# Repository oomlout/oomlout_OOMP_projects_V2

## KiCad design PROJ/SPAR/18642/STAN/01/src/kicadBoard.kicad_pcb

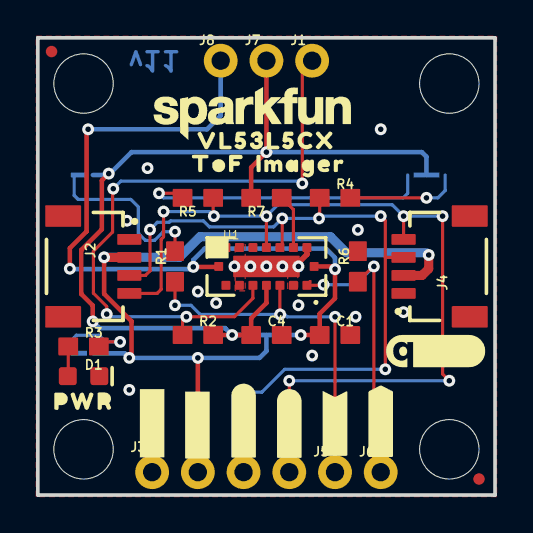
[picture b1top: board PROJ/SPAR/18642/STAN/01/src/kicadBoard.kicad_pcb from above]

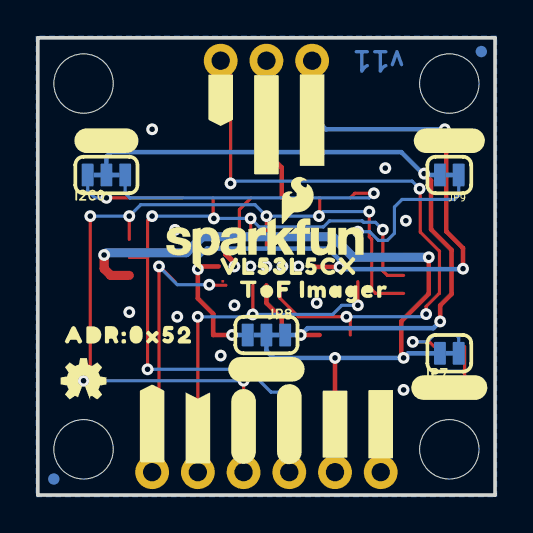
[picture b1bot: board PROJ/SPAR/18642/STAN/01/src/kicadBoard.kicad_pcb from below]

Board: 2 copper layers, 25.4 x 25.4 mm, 63 parts (25 on the bottom side), 15 nets.

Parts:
C1: 4.7uF; 0603
C4: 0.1uF; 0603
D1: RED; LED-0603
FRAME1: FRAME-LETTER; CREATIVE_COMMONS
I2C0: JUMPER-SMT_3_2-NC_TRACE_SILK; SMT-JUMPER_3_2-NC_TRACE_SILK
J1, J5, J6, J7, J8: 1X01_NO_SILK
J2, J4: JST04_1MM_RA
J3: PTH; 1X04_NO_SILK
JP1, JP2, JP5, JP6: FIDUCIALUFIDUCIAL; MICRO-FIDUCIAL
JP3, JP4, JP10, JP11: STAND-OFF
JP7: PWR_LED; SMT-JUMPER_2_NC_TRACE_SILK
JP8: PSU; SMT-JUMPER_3_2-NC_TRACE_SILK
JP9: INT; SMT-JUMPER_2_NC_TRACE_SILK
LOGO1: OSHW-LOGOMINI; OSHW-LOGO-MINI
LOGO3: QWIIC_LOGO_CONNECTOR; QWIIC_5.5MM
R1, R2, R6, R7: 47k; 0603
R3: 1k; 0603
R4, R5: 2.2k; 0603
U1: VL53L5CX
U$1: SFE_LOGO_NAME.1_INCH; SFE_LOGO_NAME_.1
U$2: SFE_LOGO_NAME_FLAME.1_INCH; SFE_LOGO_NAME_FLAME_.1
U$3, U$21: #3V3#13
U$4: PWR12
U$5: #LED#10
U$6: #INT#0
U$7: #RST#1
U$8: #INT_#0
U$9: #RST_#1
U$10: ##LP##2
U$11: #INT#1
U$12: #VDDA#0
U$13: ADR#0X520
U$14: #VDDIO#1
U$15: #PSU#0
U$16: #I�C#0
U$17, U$19: VL53L5CX0
U$18, U$22: IMAGER2
U$20, U$23: TOF1
U$24: #SCL#1
U$25: #SDA#0
U$26, U$30: #GND#62130
U$28: #SDA#62131
U$29: #SCL#62132

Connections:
3.3V: J2.2, J3.2, J4.2, JP7.2, JP8.2
GND: C1.2, C4.2, D1.C, J2.1, J3.1, J4.1, R6.2, U1.A2, U1.A6, U1.A7, U1.B4, U1.C1, U1.C6, U1.C7
INT: J5.1, R1.1, U1.A3
unnamed: I2C0.1, R5.2
unnamed: I2C0.3, R4.2
unnamed: D1.A, R3.1
unnamed: JP9.1, R1.2
unnamed: JP7.1, R3.2
unnamed: R7.1, U1.C2
RST: J6.1, R6.1, U1.A1
SCL: J2.4, J3.4, J4.4, R5.1, U1.C4
SDA: J2.3, J3.3, J4.3, R4.1, U1.C3
VDDA: C1.1, J8.1, JP8.1, U1.B1, U1.B7
VDDIO: C4.1, I2C0.2, J7.1, JP8.3, JP9.2, R2.2, R7.2, U1.A4
~LP: J1.1, R2.1, U1.A5

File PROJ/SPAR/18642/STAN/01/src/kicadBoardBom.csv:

"Id";"Designator";"Package";"Quantity";"Designation";"Supplier and ref";
1;"R2,R6,R1,R7";"0603";4;"47k";;;
2;"U$7";"#RST#1";1;"";;;
3;"U$21,U$3";"#3V3#13";2;"";;;
4;"J1,J5,J8,J6,J7";"1X01_NO_SILK";5;"";;;
5;"C4";"0603";1;"0.1uF";;;
6;"JP10,JP3,JP11,JP4";"STAND-OFF";4;"STAND-OFF";;;
7;"FRAME1";"CREATIVE_COMMONS";1;"FRAME-LETTER";;;
8;"LOGO3";"QWIIC_5.5MM";1;"QWIIC_LOGO_CONNECTOR";;;
9;"J4,J2";"JST04_1MM_RA";2;"";;;
10;"J3";"1X04_NO_SILK";1;"PTH";;;
11;"D1";"LED-0603";1;"RED";;;
12;"R3";"0603";1;"1k";;;
13;"U$17,U$19";"VL53L5CX0";2;"";;;
14;"U$26,U$30";"#GND#62130";2;"";;;
15;"U$23,U$20";"TOF1";2;"";;;
16;"JP2,JP6,JP5,JP1";"MICRO-FIDUCIAL";4;"FIDUCIALUFIDUCIAL";;;
17;"U$4";"PWR12";1;"";;;
18;"U$28";"#SDA#62131";1;"";;;
19;"U$6";"#INT#0";1;"";;;
20;"R5,R4";"0603";2;"2.2k";;;
21;"U$29";"#SCL#62132";1;"";;;
22;"U1";"VL53L5CX";1;"VL53L5CX";;;
23;"U$1";"SFE_LOGO_NAME_.1";1;"SFE_LOGO_NAME.1_INCH";;;
24;"C1";"0603";1;"4.7uF";;;
25;"U$18,U$22";"IMAGER2";2;"";;;
26;"U$2";"SFE_LOGO_NAME_FLAME_.1";1;"SFE_LOGO_NAME_FLAME.1_INCH";;;
27;"LOGO1";"OSHW-LOGO-MINI";1;"OSHW-LOGOMINI";;;
28;"U$12";"#VDDA#0";1;"";;;
29;"U$15";"#PSU#0";1;"";;;
30;"U$8";"#INT_#0";1;"";;;
31;"U$5";"#LED#10";1;"";;;
32;"JP7";"SMT-JUMPER_2_NC_TRACE_SILK";1;"PWR_LED";;;
33;"U$10";"##LP##2";1;"";;;
34;"U$24";"#SCL#1";1;"";;;
35;"JP9";"SMT-JUMPER_2_NC_TRACE_SILK";1;"INT";;;
36;"U$11";"#INT#1";1;"";;;
37;"U$14";"#VDDIO#1";1;"";;;
38;"JP8";"SMT-JUMPER_3_2-NC_TRACE_SILK";1;"PSU";;;
39;"U$25";"#SDA#0";1;"";;;
40;"I2C0";"SMT-JUMPER_3_2-NC_TRACE_SILK";1;"JUMPER-SMT_3_2-NC_TRACE_SILK";;;
41;"U$9";"#RST_#1";1;"";;;
42;"U$13";"ADR#0X520";1;"";;;
43;"U$16";"#I�C#0";1;"";;;

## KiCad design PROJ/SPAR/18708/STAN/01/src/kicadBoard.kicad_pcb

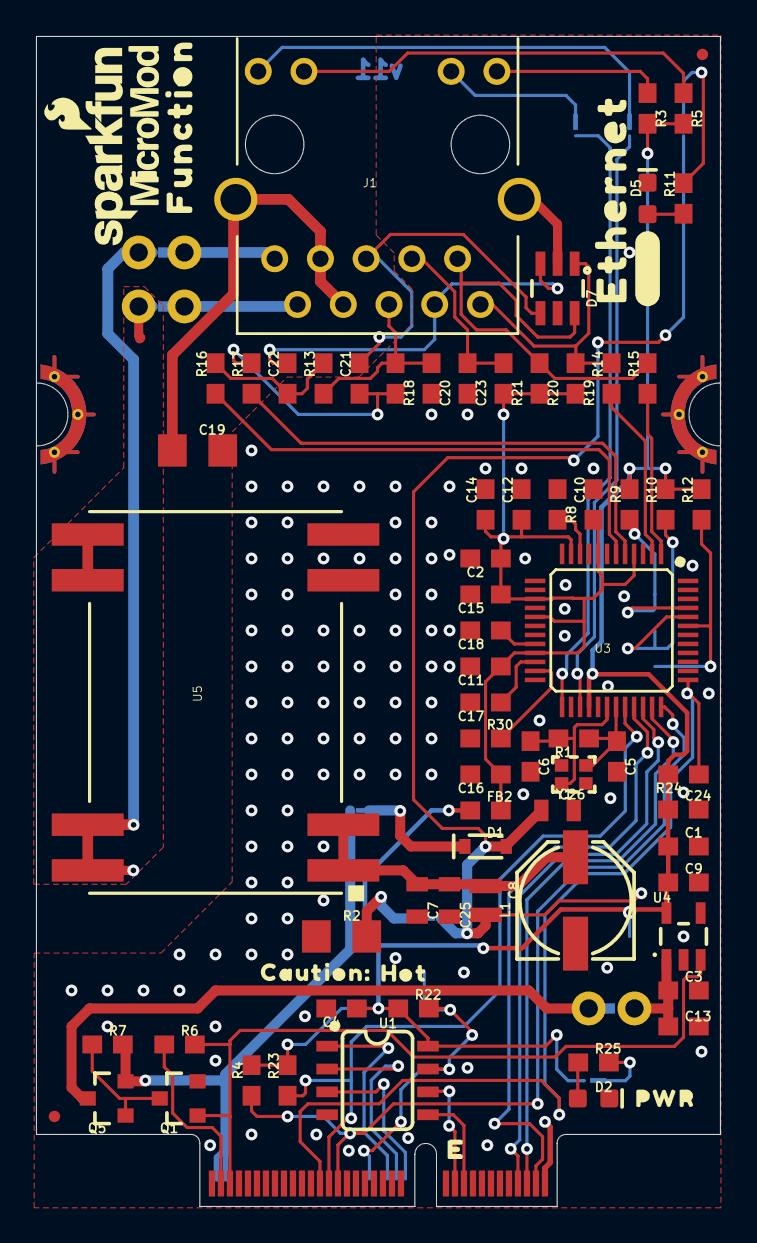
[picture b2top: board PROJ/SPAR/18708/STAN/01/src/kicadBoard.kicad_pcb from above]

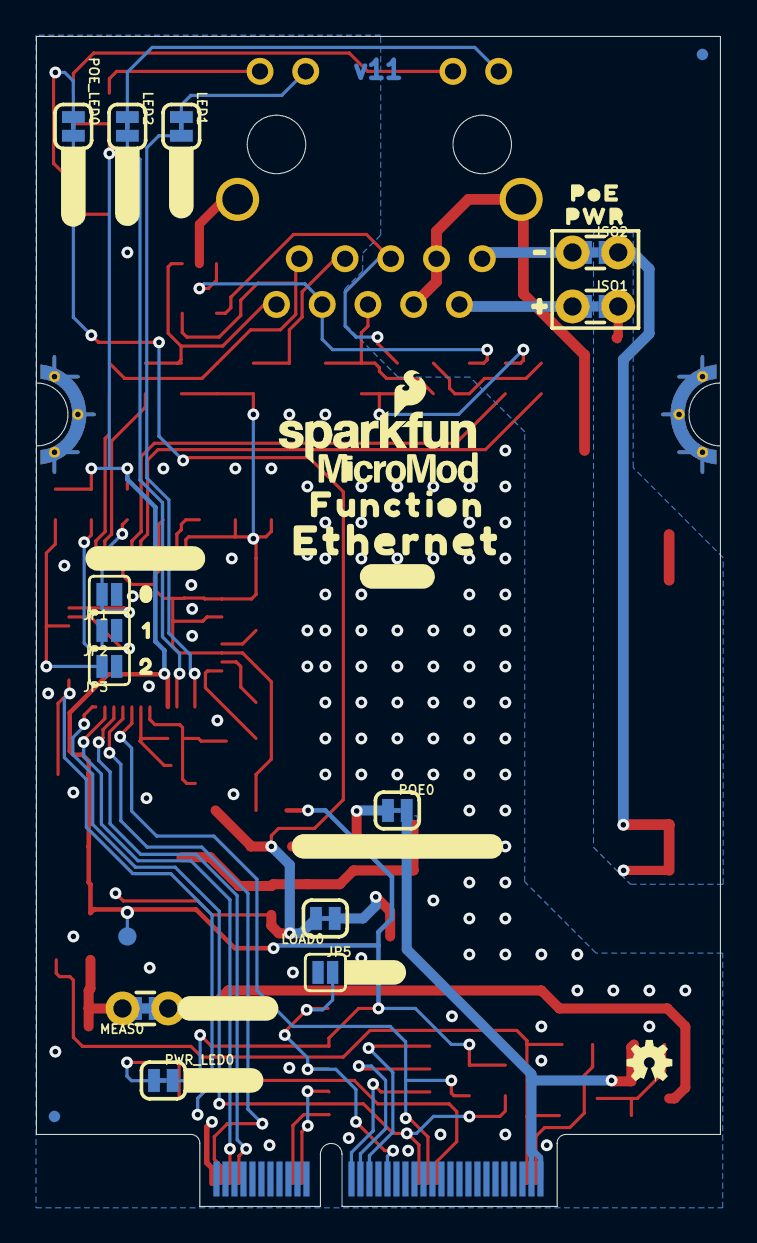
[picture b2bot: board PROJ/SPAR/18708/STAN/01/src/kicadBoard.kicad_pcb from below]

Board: 2 copper layers, 38.0 x 65.0 mm, 117 parts (38 on the bottom side), 61 nets.

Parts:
C1, C2, C3, C4, C10, C11, C12, C14, C15: 0.1uF; 0603
C5, C6: 10pF; 0603
C7, C25, C26: 10uF; 0805
C8: 100uF; PANASONIC_D
C9, C16: 10uF; 0603
C13, C24: 1.0uF; 0603
C17, C20: 10nF; 0603
C18: 4.7uF; 0603
C19: 1nF; 1206
C21, C22: 6.8nF; 0603
C23: 22nF; 0603
D1: 3A/10V/280mV; SOD-323
D2: RED; LED-0603
D5: Yellow; LED-0603
D7: DT1042-04SO; SOT-23-6
FB2: 470Ω; 0603
FD1, FD2, FD3, FD4: FIDUCIALUFIDUCIAL; FIDUCIAL-MICRO
FRAME1: FRAME-LEDGER; CREATIVE_COMMONS
ISO1, ISO2: JUMPER-COMBO_2_NC_TRACE; COMBO-JUMPER_2_NC_TRACE
J1: MAGJACK-POE; MAGJACK-SYM_LED
J11: MICROMOD_STANDARD; M.2-CARD-E-22_FUNCTION_STANDARD
JP1, JP2, JP3, JP5: JUMPER-SMT_2_NO_SILK; SMT-JUMPER_2_NO_SILK
L1: 2.2uH; 0805-WIDE
LED1, LED2: JUMPER-SMT_2_NC_TRACE_SILK; SMT-JUMPER_2_NC_TRACE_SILK
LOAD0: JUMPER-SMT_2_NC_TRACE_SILK; SMT-JUMPER_2_NC_TRACE_SILK
LOGO1, LOGO4: SFE_LOGO_NAME_FLAME.1_INCH; SFE_LOGO_NAME_FLAME_.1
LOGO2: SPECIAL_INSTRUCTIONS-ORDERING; ORDERING_INSTRUCTIONS
LOGO3: OSHW-LOGOMINI; OSHW-LOGO-MINI
MEAS0: JUMPER-COMBO_2_NC_TRACE; COMBO-JUMPER_2_NC_TRACE
POE0: SMT-JUMPER_2_NC_TRACE_SILK
POE_LED0: JUMPER-SMT_2_NC_TRACE_SILK; SMT-JUMPER_2_NC_TRACE_SILK
PWR_LED0: JUMPER-SMT_2_NC_TRACE_SILK; SMT-JUMPER_2_NC_TRACE_SILK
Q1: 220mA/50V/3.5Ω; SOT23-3
Q5: 20V/4.2A/52mΩ/1.4W; SOT23-3
R1: 1M; 0603
R2: 49.9 1/2W; 1206
R3, R5, R11, R25: 1k; 0603
R4, R6, R7, R9, R10, R12, R22, R23, R24, R30: 10k; 0603
R8: 12.4k; 0603
R13, R18, R19, R20: 49.9; 0603
R14, R15, R16, R17: 33; 0603
R21: 10; 0603
TP1: TEST-POINT3X4; PAD.03X.04
U1: EEPROM; SO08
U3: W5500; LQFP-48
U4: 3.3V; SOT23-5
U5: POE_PSU-DP990X; DP990X
U$1, U$17: ETHERNET0
U$2, U$18: #POE#0
U$3: #POWER_CARRIER#0
U$5: #DUMMY_LOAD#0
U$6: #WP#0
U$7: PWR0
U$8: #ACT#0
U$9: POE0
U$12: #LNK#1
U$13: #PMODE#0
U$14: 01
U$15: 12
U$16: 23
U$19: #0
U$20: CAUTION#0
U$21: HOT#1
U$22: #PWR#0
U$23: #_POE#0
U$24: PWR1
U$25: #1
U$26, U$27: FUNCTION0
U$28: #MEAS#3
U$37, U$63: MICROMOD_LOGO_.35
Y1: 25MHz; CRYSTAL-SMD-2.0X1.6MM

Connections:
3.3V: C1.1, C4.1, C9.1, C24.1, FB2.1, PWR_LED0.2, R3.2, R4.2, R5.2, R9.2, R10.2, R12.2, R22.1, R23.2, R24.2, TP1.1, U1.8, U3.28, U4.5
3.3V_IN: J11.73, R6.1
5V: C3.1, C13.1, MEAS0.2, MEAS0.4, U4.1
5V_FILTER: C26.1, D1.A, L1.2, LOAD0.2, POE_LED0.2
5V_RAW: C7.1, C8.+, C25.1, L1.1, U5.1, U5.2
A0: J11.36, U1.1
A1: J11.34, U1.2
A2: J11.32, U1.3
ACT_LED: LED2.2, U3.27
ETH_~CS: J11.49, R23.1, U3.32
ETH_~INT: J11.47, R4.1, U3.36
ETH_~RST: J11.51, R24.1, U3.37
EWP: J11.40, JP5.2, R22.2, U1.7
GND: C1.2, C2.2, C3.2, C4.2, C5.2, C6.2, C7.2, C8.-, C9.2, C10.2, C11.2, C12.2, C13.2, C14.2, C15.2, C16.2, C17.2, C18.2, C19.2, C20.2, C23.2, C24.2, C25.2, C26.2, D2.C, D5.C, J11.1, J11.33, J11.39, J11.45, J11.75, J11.GND1, J11.GND2, J11.GND3, J11.GND4, J11.GND5, J11.GND6, JP1.1, JP2.1, JP3.1, JP5.1, Q1.2, R2.1, R8.1, R30.1, U1.4, U3.3, U3.9, U3.14, U3.16, U3.19, U3.29, U3.48, U4.2, U5.3
GND-ISO: C19.1, D7.2, J1.7, J1.8, J1.S1, J1.S2
I2C_SCL: J11.21, U1.6
I2C_SDA: J11.19, U1.5
LINK_LED: LED1.2, U3.25
unnamed: C5.1, R1.1, U3.31, Y1.1
unnamed: C6.1, R1.2, U3.30, Y1.3
unnamed: J1.14, LED2.1
unnamed: J1.12, LED1.1
unnamed: D5.A, R11.1
unnamed: POE_LED0.1, R11.2
unnamed: D1.C, POE0.1
unnamed: J1.13, R5.1
unnamed: LOAD0.1, R2.2
unnamed: J1.11, R3.1
unnamed: Q1.3, Q5.1, R7.1
unnamed: R8.2, U3.10
unnamed: C17.1, U3.22
unnamed: C18.1, U3.20
unnamed: R30.2, U3.23
unnamed: PWR_LED0.1, R25.2
unnamed: D2.A, R25.1
PMODE0: JP1.2, R9.1, U3.45
PMODE1: JP2.2, R10.1, U3.44
PMODE2: JP3.2, R12.1, U3.43
PW1+: ISO1.2, ISO1.4, U5.5, U5.6
PW1-: ISO2.2, ISO2.4, U5.7, U5.8
PW+: ISO1.1, ISO1.3, J1.9
PW-: ISO2.1, ISO2.3, J1.10
PWR_EN: J11.71, Q1.1, R6.2, U4.3
RCT: C20.1, J1.5, R13.1, R18.1
RD+: C22.2, D7.3, J1.3
RD-: C21.2, D7.4, J1.6
RXN: R17.1, U3.5
RXN1: C21.1, R17.2, R18.2
RXP: R16.1, U3.6
RXP1: C22.1, R13.2, R16.2
SPI_CIPO: J11.7, U3.34
SPI_COPI: J11.5, U3.35
SPI_SCK: J11.3, U3.33
TCT: C23.1, J1.4, R21.1
TD+: D7.1, J1.1, R14.2, R19.1
TD-: D7.6, J1.2, R15.2, R20.1
TXN: R15.1, U3.1
TXP: R14.1, U3.2
VCC: MEAS0.1, MEAS0.3, Q5.3
VCCA: C2.1, C10.1, C11.1, C12.1, C14.1, C15.1, C16.1, FB2.2, R19.2, R20.2, R21.2, U3.4, U3.8, U3.11, U3.15, U3.17, U3.21
VCC_IN: J11.72, J11.74, POE0.2, Q5.2, R7.2

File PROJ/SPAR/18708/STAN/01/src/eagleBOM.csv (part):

"Part";"Value";"Device";"Package";"Description";"DESIGNER";"PROD_ID";"REV";"VALUE";
"C1";"0.1uF";"0.1UF-0603-25V-(+80/-20%)";"0603";"0.1µF ceramic capacitors";"";"CAP-00810";"";"0.1uF";
"C2";"0.1uF";"0.1UF-0603-25V-5%";"0603";"0.1µF ceramic capacitors";"";"CAP-08604";"";"0.1uF";
"C3";"0.1uF";"0.1UF-0603-25V-(+80/-20%)";"0603";"0.1µF ceramic capacitors";"";"CAP-00810";"";"0.1uF";
"C4";"0.1uF";"0.1UF-0603-25V-(+80/-20%)";"0603";"0.1µF ceramic capacitors";"";"CAP-00810";"";"0.1uF";
"C5";"10pF";"10PF-0603-50V-5%";"0603";"10pF ceramic capacitors";"";"CAP-11812";"";"10pF";
"C6";"10pF";"10PF-0603-50V-5%";"0603";"10pF ceramic capacitors";"";"CAP-11812";"";"10pF";
"C7";"10uF";"10UF-0805-25V-10%";"0805";"10.0µF ceramic capacitors";"";"CAP-14259";"";"10uF";
"C8";"100uF";"100UF-POLAR-25V-20%(ELEC)";"PANASONIC_D";"100µF polarized capacitors";"";"CAP-12547";"";"100uF";
"C9";"10uF";"10UF-0603-6.3V-20%";"0603";"10.0µF ceramic capacitors";"";"CAP-11015";"";"10uF";
"C10";"0.1uF";"0.1UF-0603-25V-5%";"0603";"0.1µF ceramic capacitors";"";"CAP-08604";"";"0.1uF";
"C11";"0.1uF";"0.1UF-0603-25V-5%";"0603";"0.1µF ceramic capacitors";"";"CAP-08604";"";"0.1uF";
"C12";"0.1uF";"0.1UF-0603-25V-5%";"0603";"0.1µF ceramic capacitors";"";"CAP-08604";"";"0.1uF";
"C13";"1.0uF";"1.0UF-0603-16V-10%";"0603";"1µF ceramic capacitors";"";"CAP-00868";"";"1.0uF";
"C14";"0.1uF";"0.1UF-0603-25V-5%";"0603";"0.1µF ceramic capacitors";"";"CAP-08604";"";"0.1uF";
"C15";"0.1uF";"0.1UF-0603-25V-5%";"0603";"0.1µF ceramic capacitors";"";"CAP-08604";"";"0.1uF";
"C16";"10uF";"10UF-0603-6.3V-20%";"0603";"10.0µF ceramic capacitors";"";"CAP-11015";"";"10uF";
"C17";"10nF";"10NF-0603-50V-10%";"0603";"0.01uF/10nF/10,000pF ceramic capacitors";"";"CAP-00867";"";"10nF";
"C18";"4.7uF";"4.7UF-0603-6.3V-(10%)";"0603";"4.7µF ceramic capacitors";"";"CAP-08280";"";"4.7uF";
"C19";"1nF";"1.0NF/1000PF-1206-2KV-10%";"1206";"1nF/1,000pF ceramic capacitors";"";"CAP-16238";"";"1nF";
"C20";"10nF";"10NF-0603-50V-10%";"0603";"0.01uF/10nF/10,000pF ceramic capacitors";"";"CAP-00867";"";"10nF";
"C21";"6.8nF";"6.8NF/6800PF-0603-50V-5%";"0603";"5.6nF/5600pF ceramic capacitors";"";"CAP-16239";"";"6.8nF";
"C22";"6.8nF";"6.8NF/6800PF-0603-50V-5%";"0603";"5.6nF/5600pF ceramic capacitors";"";"CAP-16239";"";"6.8nF";
"C23";"22nF";"22NF/22,000PF-0603-50V-10%";"0603";"0.022uF/22nF/22,000pF ceramic capacitors";"";"CAP-07885";"";"22nF";
"C24";"1.0uF";"1.0UF-0603-16V-10%-X7R";"0603";"1µF ceramic capacitors";"";"CAP-13930";"";"1.0uF";
"C25";"10uF";"10UF-0805-25V-10%";"0805";"10.0µF ceramic capacitors";"";"CAP-14259";"";"10uF";
"C26";"10uF";"10UF-0805-25V-10%";"0805";"10.0µF ceramic capacitors";"";"CAP-14259";"";"10uF";
"D1";"3A/10V/280mV";"DIODE-SCHOTTKY-BAT60A";"SOD-323";"Schottky diode";"";"DIO-14072";"";"3A/10V/280mV";
"D2";"RED";"LED-RED0603";"LED-0603";"Red SMD LED";"";"DIO-00819";"";"RED";
"D5";"Yellow";"LED-YELLOW0603";"LED-0603";"Yellow SMD LED";"";"DIO-09003";"";"Yellow";
"D7";"DT1042-04SO";"TVS_DIODE_ARRAYSMD";"SOT-23-6";"";"";"IC-13538";"";"ESD Diode";
"FB2";"470Ω";"FERRITE_BEAD-0603-470Ω-100MHZ-1A-200MILIΩ";"0603";"Ferrite Bead (blocks, cores, rings, chokes, etc.)";"";"NDUC-12579";"";"470Ω";
"FD1";"FIDUCIALUFIDUCIAL";"FIDUCIALUFIDUCIAL";"FIDUCIAL-MICRO";"Fiducial Alignment Points";"";"";"";"";
"FD2";"FIDUCIALUFIDUCIAL";"FIDUCIALUFIDUCIAL";"FIDUCIAL-MICRO";"Fiducial Alignment Points";"";"";"";"";
"FD3";"FIDUCIALUFIDUCIAL";"FIDUCIALUFIDUCIAL";"FIDUCIAL-MICRO";"Fiducial Alignment Points";"";"";"";"";
"FD4";"FIDUCIALUFIDUCIAL";"FIDUCIALUFIDUCIAL";"FIDUCIAL-MICRO";"Fiducial Alignment Points";"";"";"";"";
"FRAME1";"FRAME-LEDGER";"FRAME-LEDGER";"CREATIVE_COMMONS";"Schematic Frame - Ledger";"";"";"";"";
"ISO1";"JUMPER-COMBO_2_NC_TRACE";"JUMPER-COMBO_2_NC_TRACE";"COMBO-JUMPER_2_NC_TRACE";"";"";"";"";"";
"ISO2";"JUMPER-COMBO_2_NC_TRACE";"JUMPER-COMBO_2_NC_TRACE";"COMBO-JUMPER_2_NC_TRACE";"";"";"";"";"";
"J1";"MAGJACK-POE";"MAGJACK-POE";"MAGJACK-SYM_LED";"MAGJACK: RJ-45 with POE and LEDs";"";"CONN-16253";"";"";
"J11";"MICROMOD_STANDARD";"MICROMOD_STANDARD";"M.2-CARD-E-22_FUNCTION_STANDARD";"MicroMod Connector";"";"";"";"";
"JP1";"JUMPER-SMT_2_NO_SILK";"JUMPER-SMT_2_NO_SILK";"SMT-JUMPER_2_NO_SILK";"Normally open jumper";"";"";"";"";
"JP2";"JUMPER-SMT_2_NO_SILK";"JUMPER-SMT_2_NO_SILK";"SMT-JUMPER_2_NO_SILK";"Normally open jumper";"";"";"";"";
"JP3";"JUMPER-SMT_2_NO_SILK";"JUMPER-SMT_2_NO_SILK";"SMT-JUMPER_2_NO_SILK";"Normally open jumper";"";"";"";"";
"JP5";"JUMPER-SMT_2_NO_SILK";"JUMPER-SMT_2_NO_SILK";"SMT-JUMPER_2_NO_SILK";"Normally open jumper";"";"";"";"";
"L1";"2.2uH";"INDUCTOR-0805_WIDE-2.2UH";"0805-WIDE";"Inductors";"";"NDUC-14234";"";"2.2uH";
"LED1";"JUMPER-SMT_2_NC_TRACE_SILK";"JUMPER-SMT_2_NC_TRACE_SILK";"SMT-JUMPER_2_NC_TRACE_SILK";"Normally closed trace jumper";"";"";"";"";
"LED2";"JUMPER-SMT_2_NC_TRACE_SILK";"JUMPER-SMT_2_NC_TRACE_SILK";"SMT-JUMPER_2_NC_TRACE_SILK";"Normally closed trace jumper";"";"";"";"";
"LOAD";"JUMPER-SMT_2_NC_TRACE_SILK";"JUMPER-SMT_2_NC_TRACE_SILK";"SMT-JUMPER_2_NC_TRACE_SILK";"Normally closed trace jumper";"";"";"";"";
"LOGO1";"SFE_LOGO_NAME_FLAME.1_INCH";"SFE_LOGO_NAME_FLAME.1_INCH";"SFE_LOGO_NAME_FLAME_.1";"SparkFun Font Logo w/ Flame";"";"";"";"";
"LOGO2";"SPECIAL_INSTRUCTIONS-ORDERING";"SPECIAL_INSTRUCTIONS-ORDERING";"ORDERING_INSTRUCTIONS";"Special Ordering/Production Instructions Alert";"";"";"";"";
"LOGO3";"OSHW-LOGOMINI";"OSHW-LOGOMINI";"OSHW-LOGO-MINI";"Open-Source Hardware (OSHW) Logo";"";"";"";"";
"MEAS";"JUMPER-COMBO_2_NC_TRACE";"JUMPER-COMBO_2_NC_TRACE";"COMBO-JUMPER_2_NC_TRACE";"";"";"";"";"";
"POE";"";"JUMPER-SMT_2_NC_TRACE_SILK";"SMT-JUMPER_2_NC_TRACE_SILK";"Normally closed trace jumper";"";"";"";"";
"POE_LED";"JUMPER-SMT_2_NC_TRACE_SILK";"JUMPER-SMT_2_NC_TRACE_SILK";"SMT-JUMPER_2_NC_TRACE_SILK";"Normally closed trace jumper";"";"";"";"";
"PWR_LED";"JUMPER-SMT_2_NC_TRACE_SILK";"JUMPER-SMT_2_NC_TRACE_SILK";"SMT-JUMPER_2_NC_TRACE_SILK";"Normally closed trace jumper";"";"";"";"";
"Q1";"220mA/50V/3.5Ω";"MOSFET-NCH-BSS138";"SOT23-3";"N-channel MOSFETs";"";"TRANS-00830";"";"220mA/50V/3.5Ω";
"Q5";"20V/4.2A/52mΩ/1.4W";"MOSFET_PCH-DMG2305UX-7";"SOT23-3";"P-channel MOSFETs";"";"TRANS-14388";"";"20V/4.2A/52mΩ/1.4W";
"R1";"1M";"1MOHM-0603-1/4W-5%";"0603";"1MΩ resistor";"";"RES-07868";"";"1M";
"R2";"49.9 1/2W";"49.9OHM-1206-1/2W-1%";"1206";"49.9Ω resistor";"";"RES-16252";"";"";
"R3";"1k";"1KOHM-0603-1/10W-1%";"0603";"1kΩ resistor";"";"RES-07856";"";"1k";
"R4";"10k";"10KOHM-0603-1/10W-1%";"0603";"10kΩ resistor";"";"RES-00824";"";"10k";
"R5";"1k";"1KOHM-0603-1/10W-1%";"0603";"1kΩ resistor";"";"RES-07856";"";"1k";
"R6";"10k";"10KOHM-0603-1/10W-1%";"0603";"10kΩ resistor";"";"RES-00824";"";"10k";
"R7";"10k";"10KOHM-0603-1/10W-1%";"0603";"10kΩ resistor";"";"RES-00824";"";"10k";
"R8";"12.4k";"12.4KOHM-0603-1/10W-1%";"0603";"12.4kΩ resistor";"";"RES-16236";"";"12.4k";
"R9";"10k";"10KOHM-0603-1/10W-1%";"0603";"10kΩ resistor";"";"RES-00824";"";"10k";
"R10";"10k";"10KOHM-0603-1/10W-1%";"0603";"10kΩ resistor";"";"RES-00824";"";"10k";
"R11";"1k";"1KOHM-0603-1/10W-1%";"0603";"1kΩ resistor";"";"RES-07856";"";"1k";
"R12";"10k";"10KOHM-0603-1/10W-1%";"0603";"10kΩ resistor";"";"RES-00824";"";"10k";
"R13";"49.9";"49.9OHM-0603-1/10W-1%";"0603";"49.9Ω resistor";"";"RES-16237";"";"49.9";
"R14";"33";"33OHM-0603-1/10W-1%";"0603";"33Ω resistor";"";"RES-08270";"";"33";
"R15";"33";"33OHM-0603-1/10W-1%";"0603";"33Ω resistor";"";"RES-08270";"";"33";
"R16";"33";"33OHM-0603-1/10W-1%";"0603";"33Ω resistor";"";"RES-08270";"";"33";
"R17";"33";"33OHM-0603-1/10W-1%";"0603";"33Ω resistor";"";"RES-08270";"";"33";
"R18";"49.9";"49.9OHM-0603-1/10W-1%";"0603";"49.9Ω resistor";"";"RES-16237";"";"49.9";
"R19";"49.9";"49.9OHM-0603-1/10W-1%";"0603";"49.9Ω resistor";"";"RES-16237";"";"49.9";
"R20";"49.9";"49.9OHM-0603-1/10W-1%";"0603";"49.9Ω resistor";"";"RES-16237";"";"49.9";
"R21";"10";"10OHM-0603-1/10W-1%";"0603";"10Ω resistor";"";"RES-12581";"";"10";
"R22";"10k";"10KOHM-0603-1/10W-1%";"0603";"10kΩ resistor";"";"RES-00824";"";"10k";
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
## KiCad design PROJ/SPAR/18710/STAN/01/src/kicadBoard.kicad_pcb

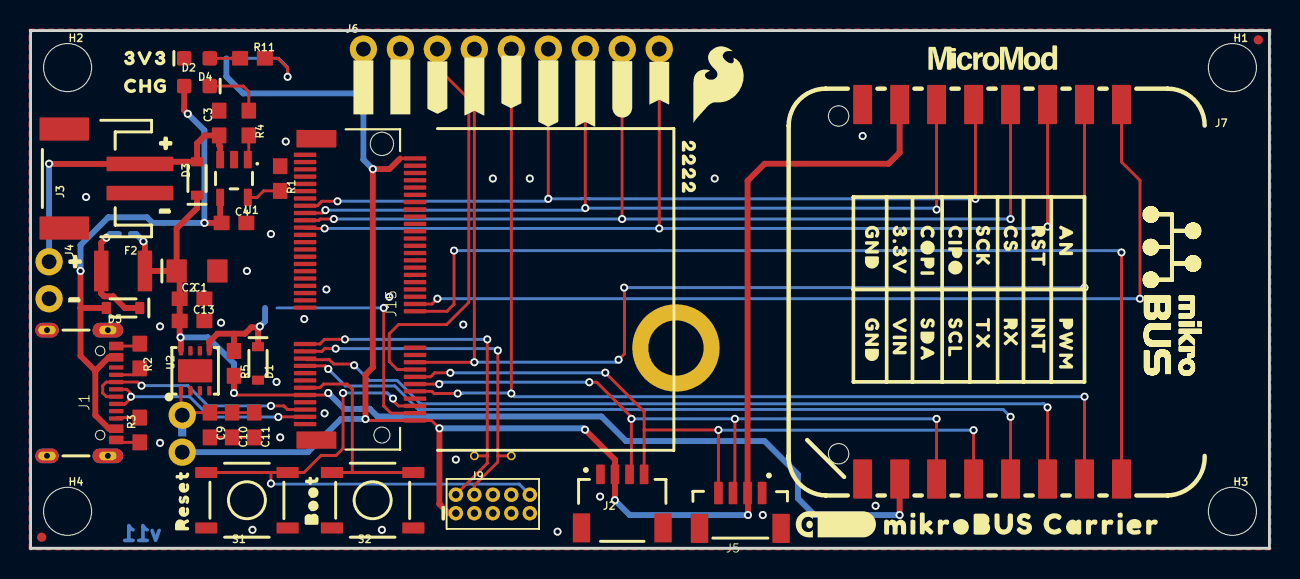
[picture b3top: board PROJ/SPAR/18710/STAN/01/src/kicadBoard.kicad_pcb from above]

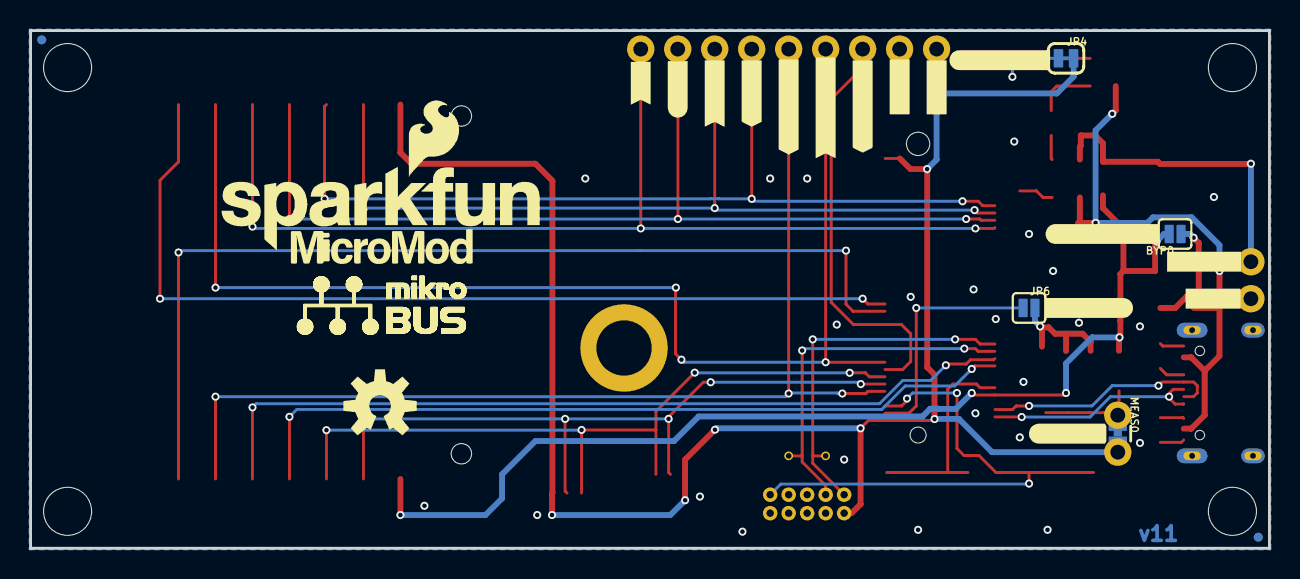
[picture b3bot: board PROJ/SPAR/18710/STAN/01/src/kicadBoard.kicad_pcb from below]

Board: 2 copper layers, 85.1 x 35.6 mm, 106 parts (25 on the bottom side), 35 nets.

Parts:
BYP0: JUMPER-SMT_2_NO_SILK; SMT-JUMPER_2_NO_SILK
C1: 0.1uF; 0603
C2: 10uF; EIA3216
C3, C4: 4.7uF; 0603
C9: 10uF; 0603
C10: 1.0uF; 0603
C11, C13: 0.22uF; 0603
D1: 3.3V; SOD-323
D2: RED; LED-0603
D3, D5: 3A/10V/280mV; SOD-323
D4: Yellow; LED-0603
F2: 6V/2A; 1210
FD1, FD2, FD3, FD4: FIDUCIALUFIDUCIAL; FIDUCIAL-MICRO
FRAME1: FRAME-LEDGER; CREATIVE_COMMONS
H1, H2, H3, H4: STAND-OFF
H5: STAND-OFF-REFLOW-M2.5_2.5MM_TALL; STAND-OFF-REFLOW-M2.5
J1: USB-C-16P-2LAYER-PADS
J2: QWIIC_RIGHT_ANGLE; JST04_1MM_RA
J3: JST-2-SMD
J4: 1X02_NO_SILK
J5: Vertical Qwiic Connector; JST04_1MM_VERT
J6: 1X09_NO_SILK
J7: MIKROBUS_SMD_BLACK1; MIKROBUS_SMD_BLACK
J9: CORTEX_JTAG_DEBUG_MINIMUM_PTH; 2X5-PTH-1.27MM
J15: MICROMOD-2222-C; M.2-CONNECTOR-E
JP4: 3V3 LED; SMT-JUMPER_2_NC_TRACE_SILK
JP6: VE; SMT-JUMPER_2_NO_SILK
LOGO1: SFE_LOGO_NAME_FLAME.2_INCH; SFE_LOGO_NAME_FLAME_.2
LOGO2: QWIIC_LOGO_CONNECTOR; QWIIC_5.5MM
LOGO3: OSHW-LOGOM; OSHW-LOGO-M
MEAS0: JUMPER-COMBO_2_NC_TRACE; COMBO-JUMPER_2_NC_TRACE
R1: 2.2k; 0603
R2, R3: 5.1k; 0603
R4, R11: 1k; 0603
R5: 100k; 0603
S1: Reset; TACTILE_SWITCH_SMD_5.2MM
S2: BOOT; TACTILE_SWITCH_SMD_5.2MM
SWDCK0: TEST-POINTTP_15TH_THRU; TP_15TH
SWDIO0: TEST-POINTTP_15TH_THRU; TP_15TH
U1: MCP73831; SOT23-5
U2: AP7361C-33FGEUDFN-8; UDFN-8
U$1: #3V3LED#0
U$2: MICROMOD_LOGO_.35
U$3: 3V30
U$4: CHG0
U$5: MIKROBUS_CARRIER0
U$6: #INT#0
U$7: MIKROBUS_LOGO
U$8, U$14, U$33: #GND#0
U$9: #MEAS#0
U$10, U$13: #3V3#0
U$11, U$32, U$36, U$37: #0
U$12: #VBAT#0
U$15: ##INT##0
U$16: #MIK_INT#0
U$17: #RST#0
U$19: #MIK_RST#0
U$20: #I2C_#INT##0
U$22, U$23: #CIPO#0
U$24, U$25: #COPI#0
U$26, U$27: #SCK#0
U$28, U$29: ##CS##0
U$30: RESET0
U$31: BOOT0
U$34: 22220
U$35: AN0
U$38: #FUSEBYP#0
U$39: #3V3EN#0
U$40: RST0
U$41: CS0
U$42: SCK0
U$43: CIPO0
U$44: SFE_LOGO_FLAME_.2
U$45: COPI0
U$46: 3#3V0
U$47, U$48: GND0
U$49: PWM0
U$50: INT0
U$51: RX0
U$52: TX0
U$53: SCL0
U$54: SDA0
U$55: VIN0
U$68: MICROMOD_LOGO_.5

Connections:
3.3V: J2.2, J5.2, J6.1, J7.7, J9.1, J15.2, J15.74, JP4.2, MEAS0.2, MEAS0.4
3.3V_EN: J15.4, JP6.1
AN: J7.1, J15.34
GND: C1.2, C2.-, C3.2, C4.2, C9.2, C10.2, C11.2, C13.2, D1.A, D2.C, H5.1, J1.GND, J1.GND2, J2.1, J3.1, J4.2, J5.1, J6.2, J7.8, J7.9, J9.3, J9.5, J9.9, J15.1, J15.7, J15.33, J15.36, J15.39, J15.45, J15.75, R1.1, R2.1, R3.1, S1.1, S1.2, S2.1, S2.2, U1.2, U2.4, U2.EP
I2C_~INT: J6.3, J15.16
MIK_INT: J6.5, J7.15, J15.10
MIK_RST: J6.4, J7.2, J15.18
unnamed: C9.1, C10.1, C11.1, MEAS0.1, MEAS0.3, U2.1
unnamed: R1.2, U1.5
unnamed: D4.C, R4.1
unnamed: JP4.1, R11.2
unnamed: D2.A, R11.1
unnamed: R4.2, U1.1
unnamed: J1.A5, R2.2
unnamed: J1.B5, R3.2
PWM: J7.16, J15.32
RX: J7.14, J15.19
SCL: J2.4, J5.4, J7.12, J15.14
SDA: J2.3, J5.3, J7.11, J15.12
SPI_CIPO: J6.6, J7.5, J15.61
SPI_COPI: J6.7, J7.6, J15.59
SPI_SCK: J6.8, J7.4, J15.57
SPI_~CS: J6.9, J7.3, J15.55
SWDCK: J9.4, J15.21, SWDCK0.1
SWDIO: J9.2, J15.23, SWDIO0.1
TX: J7.13, J15.17
USB_D+: J1.A6, J1.B6, J15.3
USB_D-: J1.A7, J1.B7, J15.5
VIN: BYP0.2, C1.1, C2.+, C13.1, D3.C, F2.2, J7.10, J15.9, R5.2, U2.8
VREG_EN: D1.C, JP6.2, R5.1, U2.5
V_BATT: C3.1, D3.A, J3.2, J4.1, U1.3
V_USB: C4.1, D4.A, D5.A, J1.VBUS1, J1.VBUS2, U1.4
V_USB_2: BYP0.1, D5.C, F2.1
~BOOT: J15.11, S2.3, S2.4
~RESET: J9.10, J15.6, S1.3, S1.4

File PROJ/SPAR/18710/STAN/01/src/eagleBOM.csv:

"Part";"Value";"Device";"Package";"Description";"DESIGNER";"PROD_ID";"REV";"SF_ID";"VALUE";
"BYP";"JUMPER-SMT_2_NO_SILK";"JUMPER-SMT_2_NO_SILK";"SMT-JUMPER_2_NO_SILK";"Normally open jumper";"";"";"";"";"";
"C1";"0.1uF";"0.1UF-0603-25V-(+80/-20%)";"0603";"0.1µF ceramic capacitors";"";"CAP-00810";"";"";"0.1uF";
"C2";"10uF";"10UF-POLAR-EIA3216-16V-10%(TANT)";"EIA3216";"10.0µF polarized capacitors";"";"CAP-00811";"";"";"10uF";
"C3";"4.7uF";"4.7UF-0603-35V-(20%)";"0603";"4.7µF ceramic capacitors";"";"CAP-14106";"";"";"4.7uF";
"C4";"4.7uF";"4.7UF-0603-35V-(20%)";"0603";"4.7µF ceramic capacitors";"";"CAP-14106";"";"";"4.7uF";
"C9";"10uF";"10UF-0603-6.3V-20%";"0603";"10.0µF ceramic capacitors";"";"CAP-11015";"";"";"10uF";
"C10";"1.0uF";"1.0UF-0603-16V-10%";"0603";"1µF ceramic capacitors";"";"CAP-00868";"";"";"1.0uF";
"C11";"0.22uF";"0.22UF-0603-25V-10%";"0603";"0.22µF ceramic capacitors";"";"CAP-07822";"";"";"0.22uF";
"C13";"0.22uF";"0.22UF-0603-25V-10%";"0603";"0.22µF ceramic capacitors";"";"CAP-07822";"";"";"0.22uF";
"D1";"3.3V";"DIODE-ZENER-MM3Z3V3T1G";"SOD-323";"Zener Diode";"";"DIO-11284";"";"";"3.3V";
"D2";"RED";"LED-RED0603";"LED-0603";"Red SMD LED";"";"DIO-00819";"";"";"RED";
"D3";"3A/10V/280mV";"DIODE-SCHOTTKY-BAT60A";"SOD-323";"Schottky diode";"";"DIO-14072";"";"";"3A/10V/280mV";
"D4";"Yellow";"LED-YELLOW0603";"LED-0603";"Yellow SMD LED";"";"DIO-09003";"";"";"Yellow";
"D5";"3A/10V/280mV";"DIODE-SCHOTTKY-BAT60A";"SOD-323";"Schottky diode";"";"DIO-14072";"";"";"3A/10V/280mV";
"F2";"6V/2A";"PPTC_6V2A";"1210";"Resettable Fuse PPTC";"";"RES-14313";"";"";"6V/2A";
"FD1";"FIDUCIALUFIDUCIAL";"FIDUCIALUFIDUCIAL";"FIDUCIAL-MICRO";"Fiducial Alignment Points";"";"";"";"";"";
"FD2";"FIDUCIALUFIDUCIAL";"FIDUCIALUFIDUCIAL";"FIDUCIAL-MICRO";"Fiducial Alignment Points";"";"";"";"";"";
"FD3";"FIDUCIALUFIDUCIAL";"FIDUCIALUFIDUCIAL";"FIDUCIAL-MICRO";"Fiducial Alignment Points";"";"";"";"";"";
"FD4";"FIDUCIALUFIDUCIAL";"FIDUCIALUFIDUCIAL";"FIDUCIAL-MICRO";"Fiducial Alignment Points";"";"";"";"";"";
"FRAME1";"FRAME-LEDGER";"FRAME-LEDGER";"CREATIVE_COMMONS";"Schematic Frame - Ledger";"";"";"";"";"";
"H1";"STAND-OFF";"STAND-OFF";"STAND-OFF";"Stand Off";"";"";"";"";"";
"H2";"STAND-OFF";"STAND-OFF";"STAND-OFF";"Stand Off";"";"";"";"";"";
"H3";"STAND-OFF";"STAND-OFF";"STAND-OFF";"Stand Off";"";"";"";"";"";
"H4";"STAND-OFF";"STAND-OFF";"STAND-OFF";"Stand Off";"";"";"";"";"";
"H5";"STAND-OFF-REFLOW-M2.5_2.5MM_TALL";"STAND-OFF-REFLOW-M2.5_2.5MM_TALL";"STAND-OFF-REFLOW-M2.5";"Stand Off Reflow Compatible";"";"HW-14899";"";"";"";
"J1";"";"USB_C_2-LAYER_PADS";"USB-C-16P-2LAYER-PADS";"USB Type C 16Pin Connector";"";"CONN-14122";"";"";"";
"J2";"QWIIC_RIGHT_ANGLE";"QWIIC_CONNECTORJS-1MM";"JST04_1MM_RA";"SparkFun I2C Standard Qwiic Connector";"";"CONN-13694";"";"";"QWIIC_RIGHT_ANGLE";
"J3";"";"JST_2MM_MALE";"JST-2-SMD";"JST 2MM MALE RA CONNECTOR";"";"CONN-11443";"";"PRT-08612";"";
"J4";"";"CONN_021X02_NO_SILK";"1X02_NO_SILK";"Multi connection point. Often used as Generic Header-pin footprint for 0.1 inch spaced/style header connections";"";"";"";"";"";
"J5";"Vertical Qwiic Connector";"QWIIC_CONNECTOR";"JST04_1MM_VERT";"SparkFun I2C Standard Qwiic Connector";"";"CONN-14483";"";"";"Vertical Qwiic Connector";
"J6";"";"CONN_09NO_SILK";"1X09_NO_SILK";"Multi connection point. Often used as Generic Header-pin footprint for 0.1 inch spaced/style header connections";"";"";"";"";"";
"J7";"MIKROBUS_SMD_BLACK1";"MIKROBUS_SMD_BLACK1";"MIKROBUS_SMD_BLACK";"";"";"CONN-16267";"";"";"";
"J9";"CORTEX_JTAG_DEBUG_MINIMUM_PTH";"CORTEX_JTAG_DEBUG_MINIMUM_PTH";"2X5-PTH-1.27MM";"Cortex Debug Connector - 10 pin";"";"";"";"";"";
"J15";"MICROMOD-2222-C";"MICROMOD-2222-C";"M.2-CONNECTOR-E";"MicroMod Connector";"";"CONN-14877";"";"";"";
"JP4";"3V3 LED";"JUMPER-SMT_2_NC_TRACE_SILK";"SMT-JUMPER_2_NC_TRACE_SILK";"Normally closed trace jumper";"";"";"";"";"";
"JP6";"VE";"JUMPER-SMT_2_NO_SILK";"SMT-JUMPER_2_NO_SILK";"Normally open jumper";"";"";"";"";"";
"LOGO1";"SFE_LOGO_NAME_FLAME.2_INCH";"SFE_LOGO_NAME_FLAME.2_INCH";"SFE_LOGO_NAME_FLAME_.2";"SparkFun Font Logo w/ Flame";"";"";"";"";"";
"LOGO2";"QWIIC_LOGO_CONNECTOR";"QWIIC_LOGO_CONNECTOR";"QWIIC_5.5MM";"Qwiic Logos for placement on schematic and PCB. The 5.5mm silk logo is best for placing next to Qwiic connector.";"";"";"";"";"";
"LOGO3";"OSHW-LOGOM";"OSHW-LOGOM";"OSHW-LOGO-M";"Open-Source Hardware (OSHW) Logo";"";"";"";"";"";
"MEAS";"JUMPER-COMBO_2_NC_TRACE";"JUMPER-COMBO_2_NC_TRACE";"COMBO-JUMPER_2_NC_TRACE";"";"";"";"";"";"";
"R1";"2.2k";"2.2KOHM-0603-1/10W-1%";"0603";"2.2kΩ resistor";"";"RES-08272";"";"";"2.2k";
"R2";"5.1k";"5.1KOHM5.1KOHM-0603-1/10W-1%";"0603";"";"";"RES-12083";"";"";"5.1k";
"R3";"5.1k";"5.1KOHM5.1KOHM-0603-1/10W-1%";"0603";"";"";"RES-12083";"";"";"5.1k";
"R4";"1k";"1KOHM-0603-1/10W-1%";"0603";"1kΩ resistor";"";"RES-07856";"";"";"1k";
"R5";"100k";"100KOHM-0603-1/10W-1%";"0603";"100kΩ resistor";"";"RES-07828";"";"";"100k";
"R11";"1k";"1KOHM-0603-1/10W-1%";"0603";"1kΩ resistor";"";"RES-07856";"";"";"1k";
"S1";"Reset";"MOMENTARY-SWITCH-SPST-SMD-5.2-TALL-REDUNDANT";"TACTILE_SWITCH_SMD_5.2MM";"Momentary Switch (Pushbutton) - SPST";"";"SWCH-14139";"";"";"";
"S2";"BOOT";"MOMENTARY-SWITCH-SPST-SMD-5.2-TALL-REDUNDANT";"TACTILE_SWITCH_SMD_5.2MM";"Momentary Switch (Pushbutton) - SPST";"";"SWCH-14139";"";"";"";
"SWDCK";"TEST-POINTTP_15TH_THRU";"TEST-POINTTP_15TH_THRU";"TP_15TH";"SparkFun Test Points";"";"";"";"";"";
"SWDIO";"TEST-POINTTP_15TH_THRU";"TEST-POINTTP_15TH_THRU";"TP_15TH";"SparkFun Test Points";"";"";"";"";"";
"U$7";"MIKROBUS_LOGO";"MIKROBUS_LOGO";"MIKROBUS_LOGO";"";"";"";"";"";"";
"U1";"MCP73831";"MCP73831";"SOT23-5";"MCP73831T Li-Ion, Li-Pol Controller";"";"IC-09995";"";"";"";
"U2";"AP7361C-33FGEUDFN-8";"AP7361C-33FGEUDFN-8";"UDFN-8";"AP7361C 3.3V LDO Regulator";"";"VREG-14094";"";"";"";

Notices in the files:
parts and their libraries:
HTTPS://CREATIVECOMMONS.ORG/LICENSES/BY-SA/4.0
RELEASED UNDER THE CREATIVE COMMONS ATTRIBUTION SHARE-ALIKE 4.0 LICENSE
